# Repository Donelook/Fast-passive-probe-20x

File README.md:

https://karas.edu.pl/?p=224 

[Fast_passive_probe_20x.pdf](https://github.com/user-attachments/files/28200651/Fast_passive_probe_20x.pdf)

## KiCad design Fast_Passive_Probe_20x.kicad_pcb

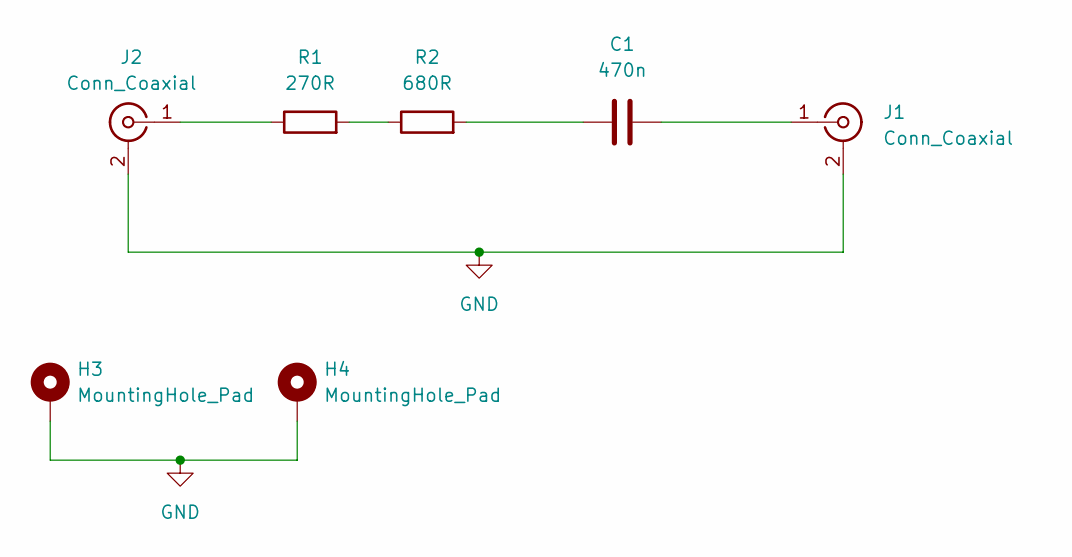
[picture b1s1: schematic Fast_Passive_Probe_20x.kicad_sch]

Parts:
C1: 470n; C_0402_1005Metric_Pad0.74x0.62mm_HandSolder
H3, H4: MountingHole_Pad; MountingHole_2.2mm_M2_DIN965_Pad
J1: Conn_Coaxial; BNC_Molex_73100-0154-50_Horizontal
J2: Conn_Coaxial; SMA_Samtec_SMA-J-P-H-ST-EM1_EdgeMount
R1: 270R; R_0402_1005Metric_Pad0.72x0.64mm_HandSolder
R2: 680R; R_0402_1005Metric_Pad0.72x0.64mm_HandSolder

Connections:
GND: H3.1, H4.1, J1.2 (Ext), J2.2 (Ext)
unnamed: C1.1, R2.2
unnamed: C1.2, J1.1 (In)
unnamed: J2.1 (In), R1.1
unnamed: R1.2, R2.1

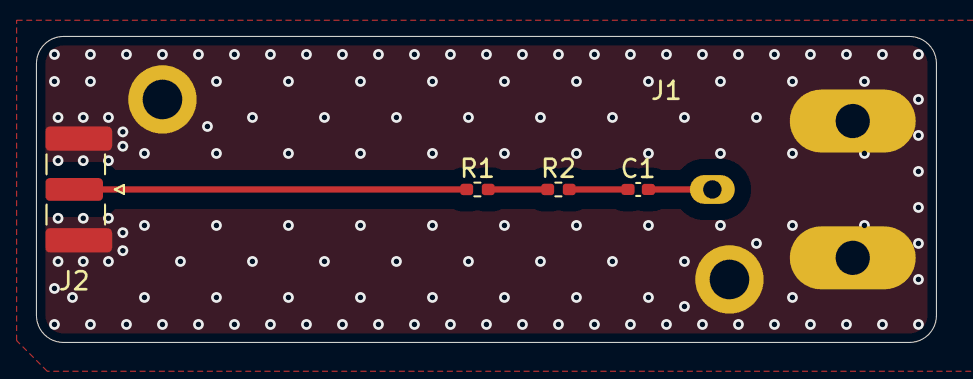
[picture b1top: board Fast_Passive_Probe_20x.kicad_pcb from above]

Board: 4 copper layers, 50.0 x 17.0 mm, 7 parts (0 on the bottom side), 5 nets.

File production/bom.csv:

Designator,Footprint,Quantity,Value,LCSC Part #
C1,0402,1,470n,
J1,BNC_Molex_73100-0154-50_Horizontal,1,Conn_Coaxial,
J2,SMA_Samtec_SMA-J-P-H-ST-EM1_EdgeMount,1,Conn_Coaxial,
R1,0402,1,270R,
R2,0402,1,680R,

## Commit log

2025-12-12 finished
2026-05-24 testy
    dodano screeny testow wygenerowano pdfa schematu
2026-05-24 Update README with resource links and images
    Added links to resources and images in README.
